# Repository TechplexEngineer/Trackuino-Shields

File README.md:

Trackuino-Shields
=================

Updated version of the trackuino shields to use all through hole components

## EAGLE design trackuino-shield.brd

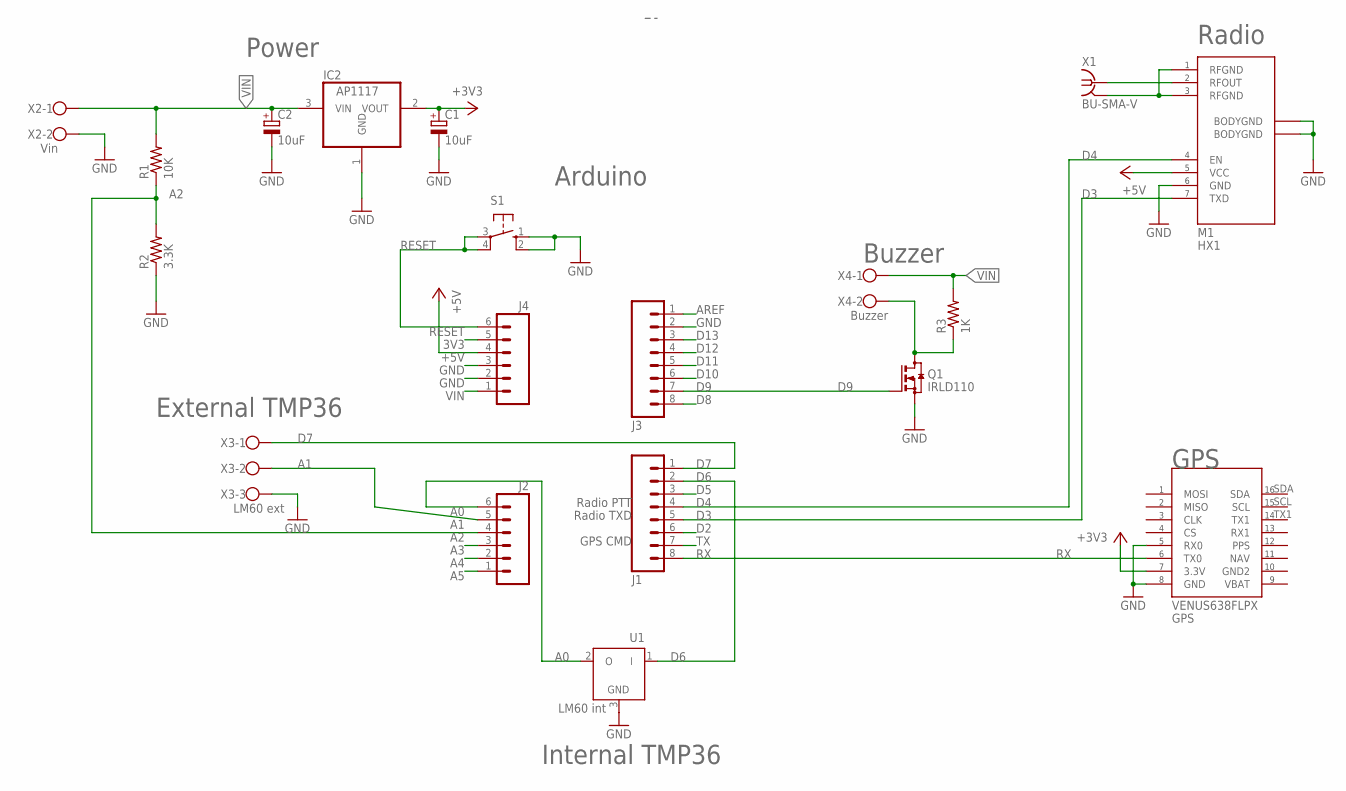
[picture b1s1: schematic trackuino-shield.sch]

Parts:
C1, C2: 10uF; E2,5-5
GPS: VENUS638FLPX
IC2: AP1117; TO220-3
J1, J3: M081X08; 1X08
J2, J4: M06SIP; 1X06
M1: HX1
Q1: IRLD110; HVMDIP
R1: 10K; 0207/7
R2: 3.3K; 0207/7
R3: 1K; 0207/7
S1: 10-XX; B3F-10XX
U1: LM60 int; TO92
X1: BU-SMA-V
X2: Vin; W237-102
X3: LM60 ext; W237-103
X4: Buzzer; W237-102

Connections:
3V3: J4.5
+3V3: C1.+, GPS.3.3V, IC2.2 (VOUT)
+5V: J4.4, M1.VCC
A0: J2.6, U1.2 (O)
A1: J2.5, X3.2
A2: J2.4, R1.1, R2.2
A3: J2.3
A4: J2.2
A5: J2.1
AREF: J3.1
D2: J1.6
D3: J1.5, M1.TXD
D4: J1.4, M1.EN
D5: J1.3
D6: J1.2, U1.1 (I)
D7: J1.1, X3.1
D8: J3.8
D9: J3.7, Q1.G
D10: J3.6
D11: J3.5
D12: J3.4
D13: J3.3
GND: C1.-, C2.-, GPS.GND, GPS.RX0, IC2.1 (GND), J3.2, J4.2, J4.3, M1.0V (GND), M1.BODYGND1 (BODYGND), M1.BODYGND2 (BODYGND), Q1.S, R2.1, S1.1 (S), S1.2 (S1), U1.3 (GND), X2.2, X3.3
unnamed: Q1.D@1 (D), Q1.D@2 (D), R3.1, X4.2
unnamed: M1.RFOUT, X1.1
RESET: J4.6, S1.3, S1.4 (P1)
RFGND: M1.RFGND1 (RFGND), M1.RFGND2 (RFGND), X1.2, X1.3 (2), X1.4 (2), X1.5 (2)
RX: GPS.TX0, J1.8
TX: J1.7
VIN: C2.+, IC2.3 (VIN), J4.1, R1.2, R3.2, X2.1, X4.1

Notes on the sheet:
Power
Arduino
Radio
GPS
Internal TMP36
Buzzer
Radio PTT
Radio TXD
GPS CMD
External TMP36

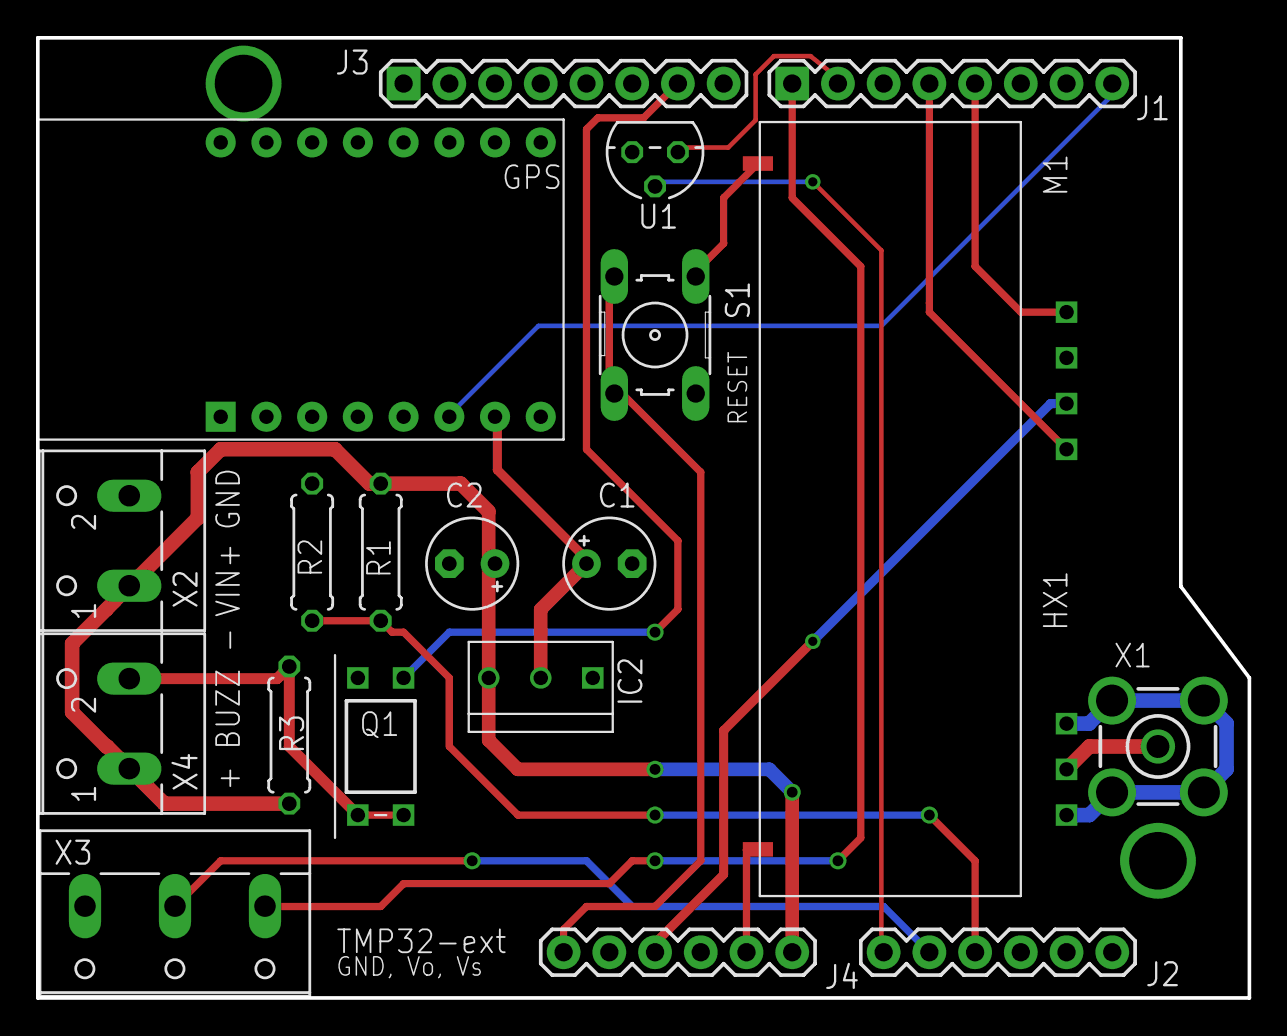
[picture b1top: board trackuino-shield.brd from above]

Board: 2 copper layers, 67.3 x 53.3 mm, 20 parts (0 on the bottom side), 17 nets.

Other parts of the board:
U$1: FLAGS_SM

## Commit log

2013-11-19 Trackuino @ 2.2
2013-11-19 removing the level shifters
2013-12-01 Successfully replaced all surface mount components.
2013-12-12 Placed buzzer mosfet. All surface mount components have been removed
2013-12-18 Adding information about mouser order and parts
2013-12-18 Removing old gerber files
2013-12-18 Minor routing change
2013-12-18 Reorg schematic and removed TX to GPS
2013-12-18 Fixed an airwire
2013-12-28 Fixed sheaff's comments and separated the ground plane from the radiometrix
2014-01-01 Added logo
2014-01-15 Adding schematic PDF
2014-01-15 removing old pdf
2014-01-17 Moved via so it won't short with the radiometrix

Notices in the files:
parts and their libraries:
SparkFun-Connectors: Licensing: CC v3.0 Share-Alike You are welcome to use this library for commercial purposes.
